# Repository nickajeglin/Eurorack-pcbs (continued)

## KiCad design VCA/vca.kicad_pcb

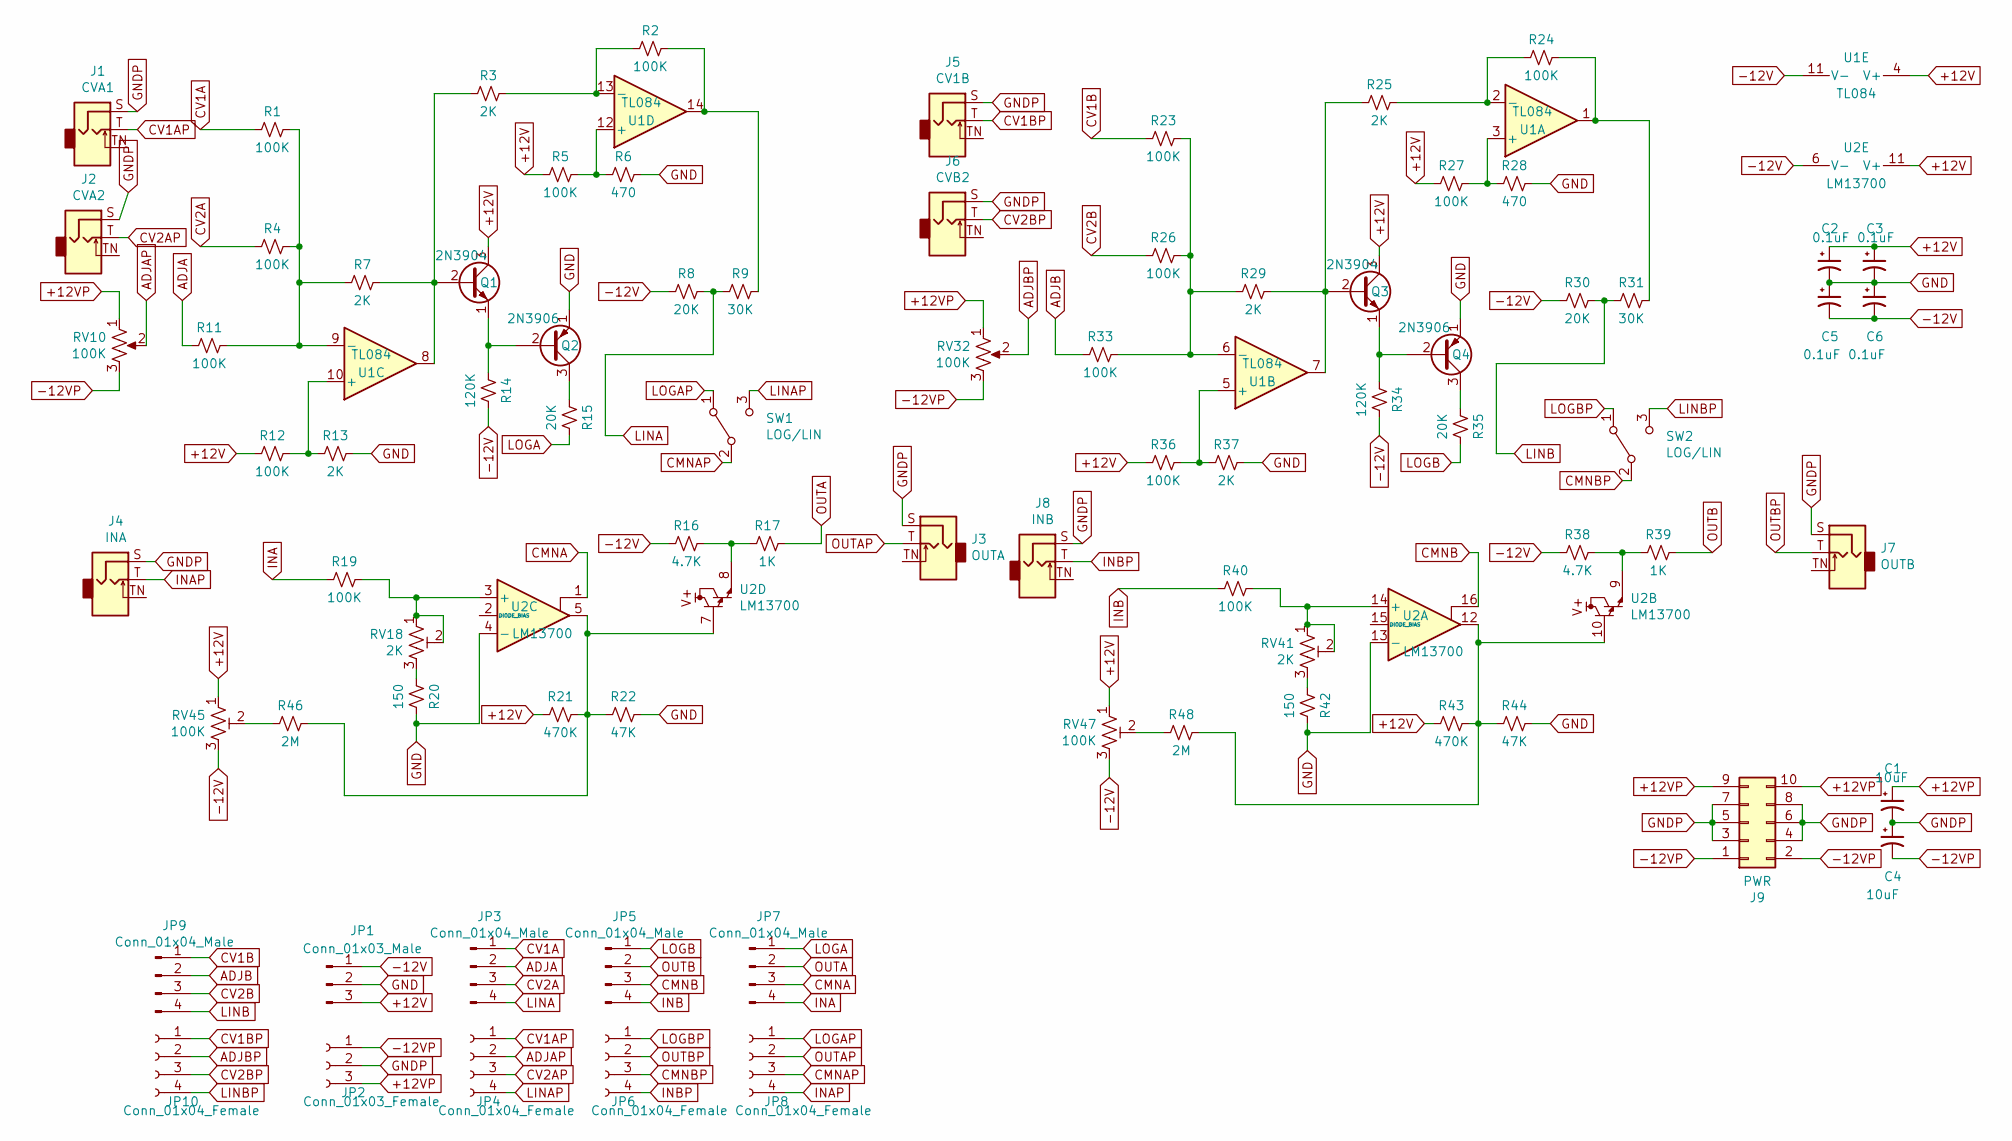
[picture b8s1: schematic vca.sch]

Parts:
C1, C4: 10uF; CP_Radial_D5.0mm_P2.50mm
C2, C3, C5, C6: 0.1uF; C_1206_3216Metric_Pad1.42x1.75mm_HandSolder
J1: CVA1; Jack_3.5mm_QingPu_WQP-PJ398SM_Vertical_CircularHoles
J2: CVA2; Jack_3.5mm_QingPu_WQP-PJ398SM_Vertical_CircularHoles
J3: OUTA; Jack_3.5mm_QingPu_WQP-PJ398SM_Vertical_CircularHoles
J4: INA; Jack_3.5mm_QingPu_WQP-PJ398SM_Vertical_CircularHoles
J5: CV1B; Jack_3.5mm_QingPu_WQP-PJ398SM_Vertical_CircularHoles
J6: CVB2; Jack_3.5mm_QingPu_WQP-PJ398SM_Vertical_CircularHoles
J7: OUTB; Jack_3.5mm_QingPu_WQP-PJ398SM_Vertical_CircularHoles
J8: INB; Jack_3.5mm_QingPu_WQP-PJ398SM_Vertical_CircularHoles
J9: PWR; IDC-Header_2x05_P2.54mm_Vertical
JP1: Conn_01x03_Male; PinHeader_1x03_P2.54mm_Vertical
JP2: Conn_01x03_Female; PinHeader_1x03_P2.54mm_Vertical
JP3, JP5, JP7, JP9: Conn_01x04_Male; PinHeader_1x04_P2.54mm_Vertical
JP4, JP6, JP8, JP10: Conn_01x04_Female; PinHeader_1x04_P2.54mm_Vertical
Q1, Q3: 2N3904; TO-92_Inline
Q2, Q4: 2N3906; TO-92_Inline
R1, R2, R4, R5, R11, R12, R19, R23, R24, R26, R27, R33, R36, R40: 100K; R_1206_3216Metric_Pad1.42x1.75mm_HandSolder
R3, R7, R13, R25, R29, R37: 2K; R_1206_3216Metric_Pad1.42x1.75mm_HandSolder
R6, R28: 470; R_1206_3216Metric_Pad1.42x1.75mm_HandSolder
R8, R15, R30, R35: 20K; R_1206_3216Metric_Pad1.42x1.75mm_HandSolder
R9, R31: 30K; R_1206_3216Metric_Pad1.42x1.75mm_HandSolder
R14, R34: 120K; R_1206_3216Metric_Pad1.42x1.75mm_HandSolder
R16, R38: 4.7K; R_1206_3216Metric_Pad1.42x1.75mm_HandSolder
R17, R39: 1K; R_1206_3216Metric_Pad1.42x1.75mm_HandSolder
R20, R42: 150; R_1206_3216Metric_Pad1.42x1.75mm_HandSolder
R21, R43: 470K; R_1206_3216Metric_Pad1.42x1.75mm_HandSolder
R22, R44: 47K; R_1206_3216Metric_Pad1.42x1.75mm_HandSolder
R46, R48: 2M; R_1206_3216Metric_Pad1.42x1.75mm_HandSolder
RV10, RV32: 100K; Potentiometer_Bourns_PTV09A-1_Single_Vertical
RV18, RV41: 2K; Potentiometer_Bourns_3266Y_Vertical
RV45, RV47: 100K; Potentiometer_Bourns_3266Y_Vertical
SW1, SW2: LOG/LIN; toggle_switch_mini
U1: TL084; SOIC-14_3.9x8.7mm_P1.27mm
U2: LM13700; SOIC-16_4.55x10.3mm_P1.27mm

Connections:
+12V: C2.1, C3.1, JP1.3, Q1.3 (C), Q3.3 (C), R5.2, R12.2, R21.2, R27.2, R36.2, R43.2, RV45.1, RV47.1, U1.4 (V+), U2.11 (V+)
+12VP: C1.1, J9.9, J9.10, JP2.3, RV10.1, RV32.1
-12V: C5.2, C6.2, JP1.1, R8.2, R14.1, R16.2, R30.2, R34.1, R38.2, RV45.3, RV47.3, U1.11 (V-), U2.6 (V-)
-12VP: C4.2, J9.1, J9.2, JP2.1, RV10.3, RV32.3
ADJA: JP3.2, R11.2
ADJAP: JP4.2, RV10.2
ADJB: JP9.2, R33.2
ADJBP: JP10.2, RV32.2
CMNA: JP7.3, U2.1
CMNAP: JP8.3, SW1.2 (B)
CMNB: JP5.3, U2.16
CMNBP: JP6.3, SW2.2 (B)
CV1A: JP3.1, R1.2
CV1AP: J1.T, JP4.1
CV1B: JP9.1, R23.2
CV1BP: J5.T, JP10.1
CV2A: JP3.3, R4.2
CV2AP: J2.T, JP4.3
CV2B: JP9.3, R26.2
CV2BP: J6.T, JP10.3
GND: C2.2, C3.2, C5.1, C6.1, JP1.2, Q2.1 (E), Q4.1 (E), R6.1, R13.1, R20.1, R22.1, R28.1, R37.1, R42.1, R44.1, U2.4 (-), U2.13 (-)
GNDP: C1.2, C4.1, J1.S, J2.S, J3.S, J4.S, J5.S, J6.S, J7.S, J8.S, J9.3, J9.4, J9.5, J9.6, J9.7, J9.8, JP2.2
INA: JP7.4, R19.2
INAP: J4.T, JP8.4
INB: JP5.4, R40.2
INBP: J8.T, JP6.4
LINA: JP3.4, R8.1, R9.2
LINAP: JP4.4, SW1.3 (C)
LINB: JP9.4, R30.1, R31.2
LINBP: JP10.4, SW2.3 (C)
LOGA: JP7.1, R15.1
LOGAP: JP8.1, SW1.1 (A)
LOGB: JP5.1, R35.1
LOGBP: JP6.1, SW2.1 (A)
unnamed: Q1.1 (E), Q2.2 (B), R14.2
unnamed: Q1.2 (B), R3.2, R7.1, U1.8
unnamed: Q2.3 (C), R15.2
unnamed: Q3.1 (E), Q4.2 (B), R34.2
unnamed: Q3.2 (B), R25.2, R29.1, U1.7
unnamed: Q4.3 (C), R35.2
unnamed: R1.1, R4.1, R7.2, R11.1, U1.9 (-)
unnamed: R2.1, R9.1, U1.14
unnamed: R2.2, R3.1, U1.13 (-)
unnamed: R5.1, R6.2, U1.12 (+)
unnamed: R12.1, R13.2, U1.10 (+)
unnamed: R16.1, R17.2, U2.8
unnamed: R19.1, RV18.1, RV18.2, U2.3 (+)
unnamed: R20.2, RV18.3
unnamed: R21.1, R22.2, R46.1, U2.5, U2.7
unnamed: R23.1, R26.1, R29.2, R33.1, U1.6 (-)
unnamed: R24.1, R31.1, U1.1
unnamed: R24.2, R25.1, U1.2 (-)
unnamed: R27.1, R28.2, U1.3 (+)
unnamed: R36.1, R37.2, U1.5 (+)
unnamed: R38.1, R39.2, U2.9
unnamed: R40.1, RV41.1, RV41.2, U2.14 (+)
unnamed: R42.2, RV41.3
unnamed: R43.1, R44.2, R48.1, U2.10, U2.12
unnamed: R46.2, RV45.2
unnamed: R48.2, RV47.2
OUTA: JP7.2, R17.1
OUTAP: J3.T, JP8.2
OUTB: JP5.2, R39.1
OUTBP: J7.T, JP6.2

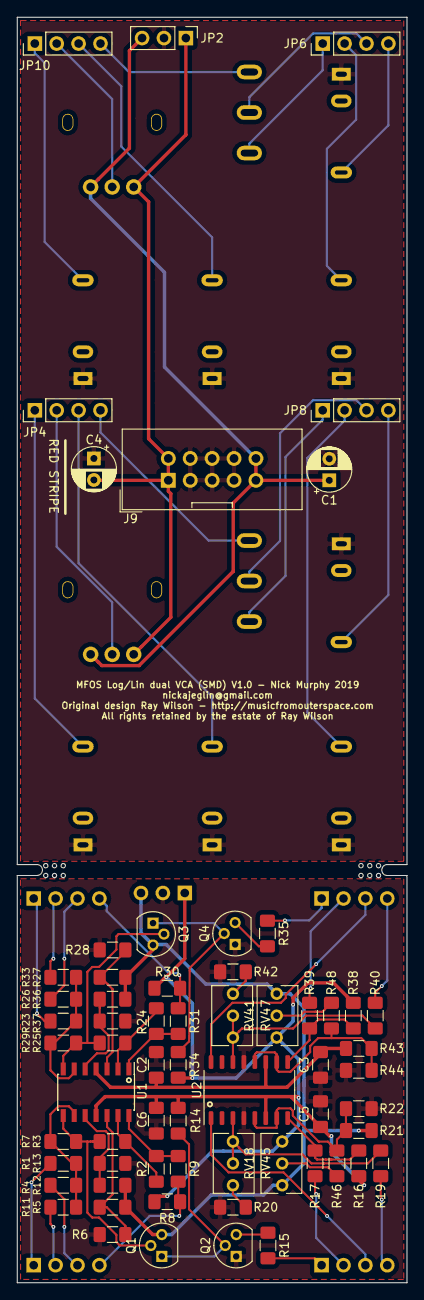
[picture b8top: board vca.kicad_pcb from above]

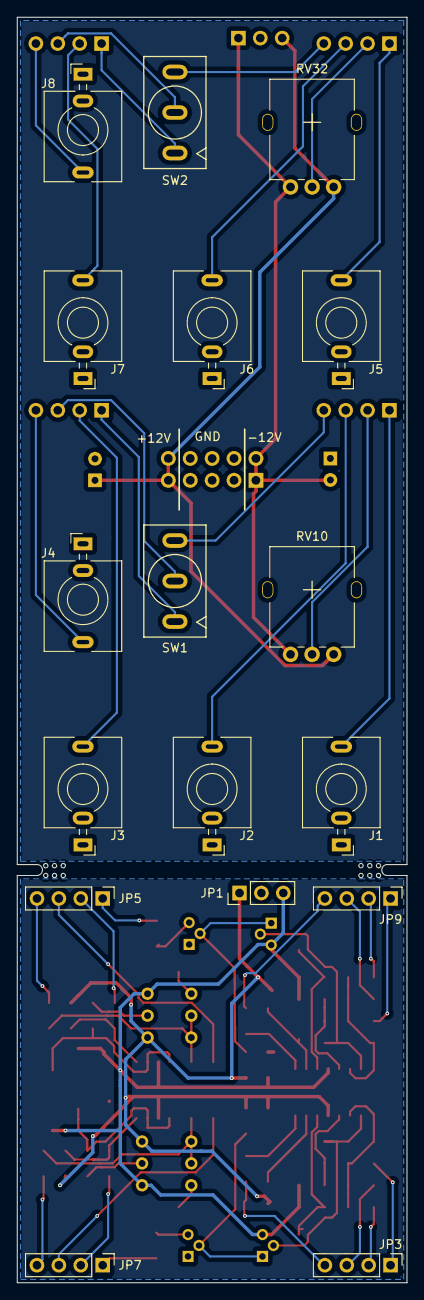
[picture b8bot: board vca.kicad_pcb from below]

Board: 2 copper layers, 45.2 x 146.8 mm, 81 parts (17 on the bottom side), 64 nets.

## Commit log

2019-02-28 Add files via upload
    Corrected reversed log/lin text on faceplate ink.
2019-03-05 Add files via upload
    Fixed reversed pot leads and C12 silk polarity. Cleaned up some power routing.
2019-03-05 Update README.md
    Added changes for VCO V2.0
2019-03-05 Add files via upload
    Adding Gerbers
2019-10-01 Update README.md
    added info about logic module
2019-10-04 Inital release
2019-10-23 Add files via upload
    Moved pots closer together. Adjusted faceplate files to match.
2025-01-03 Over and out
    o7
